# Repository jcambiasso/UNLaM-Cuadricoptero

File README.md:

# UNLaM-Cuadricoptero
Proyecto para la cátedra de tecnología electrónica

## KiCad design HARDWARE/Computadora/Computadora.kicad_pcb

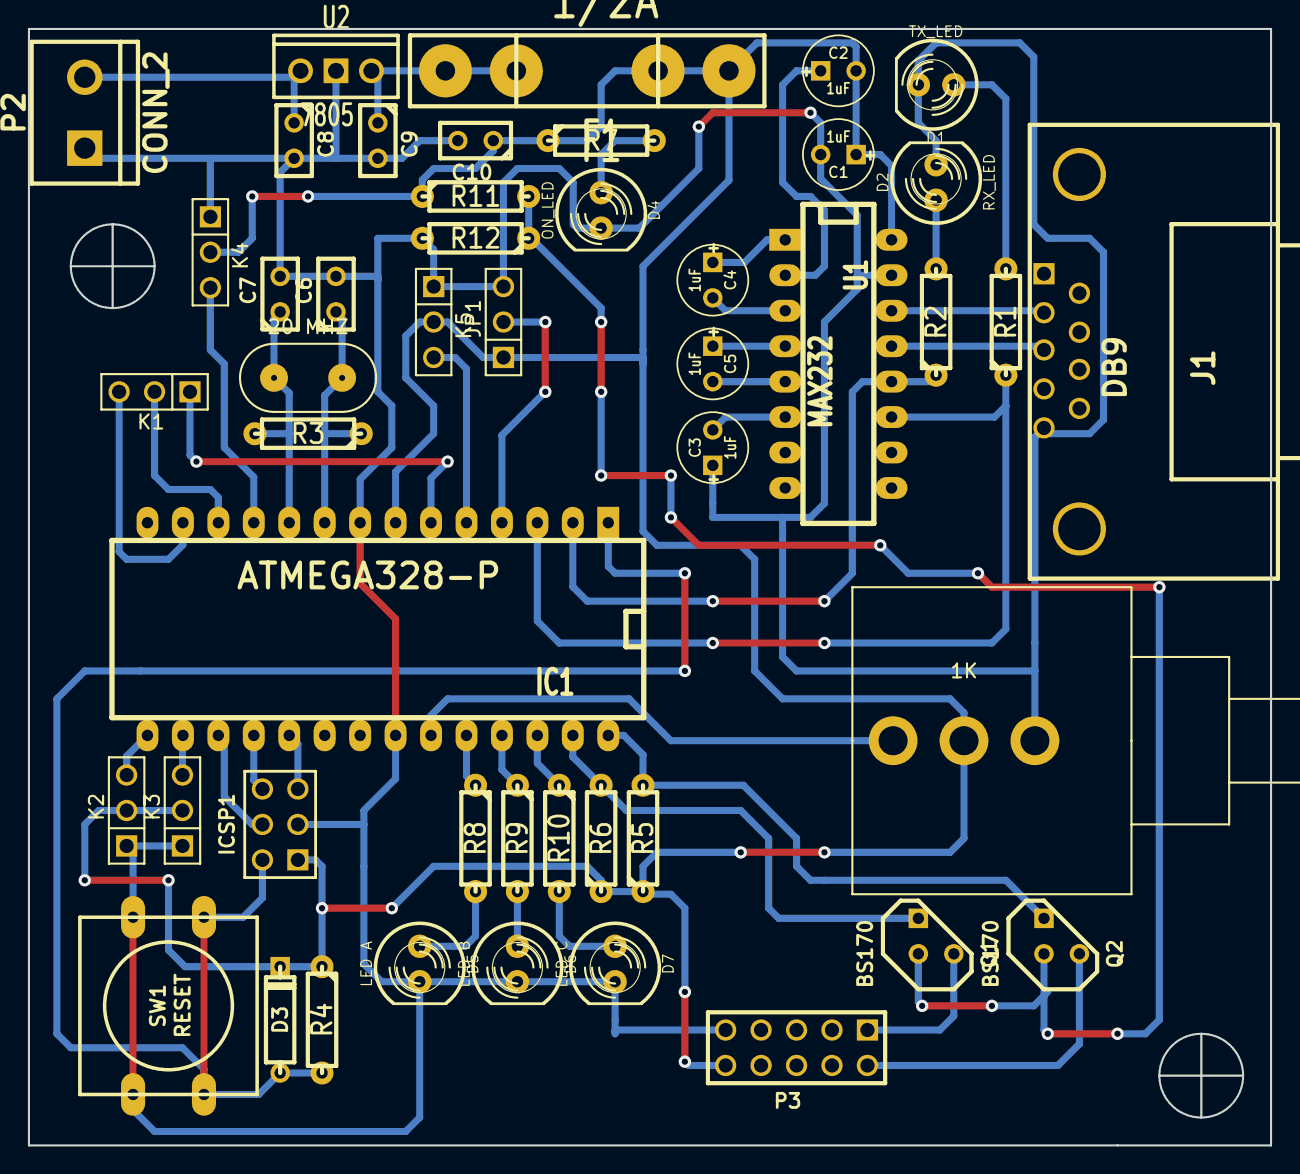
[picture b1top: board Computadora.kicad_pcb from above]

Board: 2 copper layers, 89.0 x 80.0 mm, 48 parts (0 on the bottom side), 43 nets.

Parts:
C1, C2, C3, C4, C5: 1uF; C1V5
C6: 12pF; C1
C7: 22pF; C1
C8: 0.33uF; C1
C9, C10: 0.1uF; C1
D1: TX_LED; LED-5MM
D2: RX_LED; LED-5MM
D3: DIODE; D3
D4: ON_LED; LED-5MM
D5: LED A; LED-5MM
D6: LED B; LED-5MM
D7: LED C; LED-5MM
F1: 1/2A; FUSE5-20
IC1: ATMEGA328-P; DIP-28__600_ELL
ICSP1: CONN_3X2; pin_array_3x2corregido
J1: DB9; DB9FC
JP1: DEBUG MODE SW; PIN_ARRAY_3X1
K1: AUX_PINS; PIN_ARRAY_3X1
K2, K3, K4, K5: CONN_3; PIN_ARRAY_3X1
P2: CONN_2; bornier2
P3: CONN_SENSORES; PIN_ARRAY_5x2
Q1, Q2: BS170; TO92DGS
R1, R2, R7, R8, R9, R10: 1k; R3-LARGE_PADS
R3: 1M; R3-LARGE_PADS
R4: 10k; R3-LARGE_PADS
R5, R6: 4.7k; R3-LARGE_PADS
R11, R12: 4.7K; R3-LARGE_PADS
RV1: 1K; Pote10Vueltas
SW1: RESET; SW_PUSH-12mm
U1: MAX232; DIP-16__300_ELL
U2: 7805; LM78XXV
X1: 20 MHZ; xtal

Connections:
+2.5V: Q1.G, Q2.G, R11.2, R12.1
+5V: C1.1, C2.2, C10.1, D3.2, F1.2, IC1.7, ICSP1.1, JP1.1, K2.2, K3.2, K4.2, K5.2, P3.10, R4.1, R5.1, R6.1, R7.1, R11.1, RV1.1, U1.16
+12V: C8.1, P2.2, U2.VI
/DEBUG: IC1.4, JP1.2
/LA: IC1.24, R8.1
/LB: IC1.25, R9.1
/LC: IC1.26, R10.1
/MISO: IC1.18, ICSP1.6
/MOSI: IC1.17, ICSP1.4
/PWM1: IC1.15, K2.3
/PWM2: IC1.16, K3.3
/PWM3: IC1.11, K4.3
/PWM4: IC1.5, K5.3
/RESET: D3.1, IC1.1, ICSP1.2, R4.2, SW1.2
/RX: IC1.2, R2.1, U1.12
/SCK: IC1.19, ICSP1.5
/SCL: IC1.28, Q2.D, R5.2
/SDA: IC1.27, Q1.D, R6.2
/SP: IC1.23, RV1.2
/TX: IC1.3, R1.1, U1.11
/XTAL1: C6.1, IC1.9, R3.1, X1.2
/XTAL2: C7.1, IC1.10, R3.2, X1.1
GND: C1.2, C3.1, C6.2, C7.2, C8.2, C9.2, C10.2, D1.2, D2.2, D4.2, D5.2, D6.2, D7.2, IC1.8, IC1.22, ICSP1.3, J1.5, JP1.3, K2.1, K3.1, K4.1, K5.1, P2.1, P3.9, R12.2, RV1.3, SW1.1, U1.15, U2.GND
unnamed: IC1.13, K1.3
unnamed: IC1.6, K1.1
unnamed: IC1.12, K1.2
unnamed: D4.1, R7.2
unnamed: C9.1, F1.1, U2.VO
unnamed: P3.2, Q2.S
unnamed: P3.1, Q1.S
unnamed: D7.1, R10.2
unnamed: D6.1, R9.2
unnamed: D5.1, R8.2
unnamed: J1.3, U1.13
unnamed: J1.2, U1.14
unnamed: C5.2, U1.5
unnamed: C5.1, U1.4
unnamed: C4.2, U1.3
unnamed: C4.1, U1.1
unnamed: C3.2, U1.6
unnamed: C2.1, U1.2
unnamed: D2.1, R2.2
unnamed: D1.1, R1.2

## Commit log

2015-07-19 Se crean carpetas y proyecto kicad para la placa de la computadora de abordo
2015-07-20 Se seleccionan footprints, faltan algunos
2015-07-20 Se elimina el footprint del capacitor realizado por Gonzalo Vaca
2015-07-21 Se completan los footprints y se genera un pcb para validarlos
2015-07-22 Se termina primera version del pcb. yeah!
2015-07-23 Se hace una nueva placa y circuito esquemático separando los motores
